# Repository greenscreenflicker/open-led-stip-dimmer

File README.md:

# open-led-stip-dimmer
This is an open led stipe dimmer for MakerCon 2017 (16.2-18.2) in Heidelberg, Germany.
The project is used as sample project to explain the basics of PCB layout.

# Tutorial
The script (in German) can be found in the folder "doc".

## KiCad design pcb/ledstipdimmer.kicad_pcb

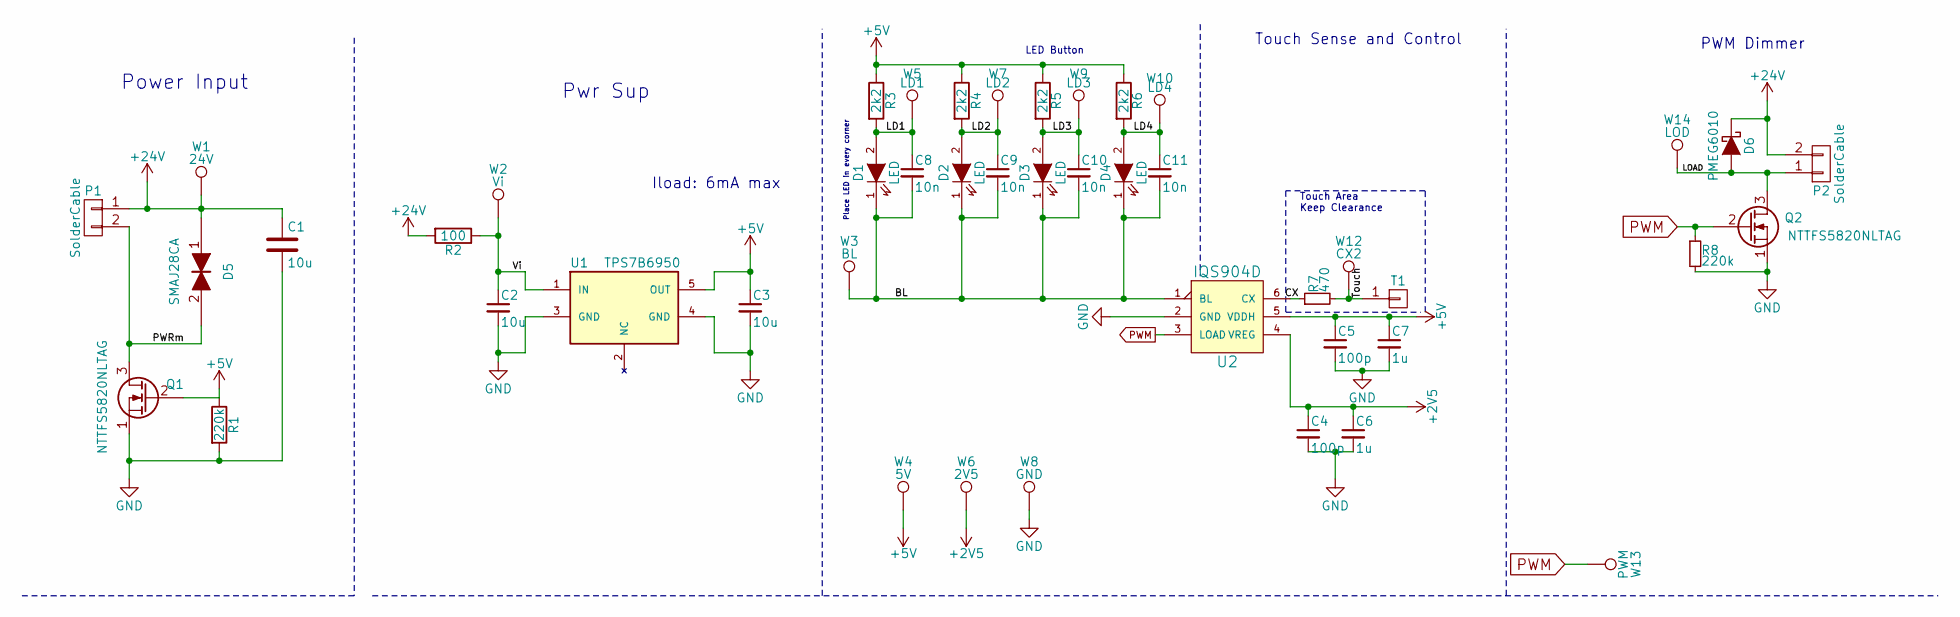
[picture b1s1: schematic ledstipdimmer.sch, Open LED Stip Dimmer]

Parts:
C1, C2: 10u; SMD-C-1206; Voltage 50V
C3: 10u; SMD-C-0603; Voltage 10V
C4, C5: 100p; SMD-C-0603; Voltage 10V
C6, C7: 1u; SMD-C-0603; Voltage 10V
C8, C9, C10, C11: 10n; SMD-C-0603; Voltage 50V
D1, D2, D3, D4: LED; LED_1206_revmnt
D5: SMAJ28CA; SMA_Bipolar
D6: PMEG6010; SOD-123
P1, P2: SolderCable; solder_cable_2
Q1, Q2: NTTFS5820NLTAG; WDFN8_3.3x3.3
R1, R8: 220k; SMD-R-0603
R2: 100; SMD-R-0603
R3, R4, R5, R6: 2k2; SMD-R-0603
R7: 470; SMD-R-0603
T1: TOUCH; touch15x15
U1: TPS7B6950; SOT-23-5; Mouser# 595-TPS7B6950DBVR
U2: IQS904D; SOT-23-6; Mouser# IQS904D-00000TSR
W1: 24V; RECP_709150001050006
W2: Vi; RECP_709150001050006
W3: BL; RECP_709150001050006
W4: 5V; RECP_709150001050006
W5: LD1; RECP_709150001050006
W6: 2V5; RECP_709150001050006
W7: LD2; RECP_709150001050006
W8: GND; RECP_709150001050006
W9: LD3; RECP_709150001050006
W10: LD4; RECP_709150001050006
W12: CX2; RECP_709150001050006
W13: PWM; RECP_709150001050006
W14: LOD; RECP_709150001050006

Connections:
+2V5: C4.1, C6.1, U2.4 (VREG), W6.1
+5V: C3.1, C5.1, C7.1, Q1.2 (G), R1.1, R3.1, R4.1, R5.1, R6.1, U1.5 (OUT), U2.5 (VDDH), W4.1
+24V: C1.1, D5.1, D6.1 (K), P1.1, P2.2, R2.2, W1.1
/BL: C8.2, C9.2, C10.2, C11.2, D1.1 (K), D2.1 (K), D3.1 (K), D4.1 (K), U2.1 (BL), W3.1
/CX: R7.1, U2.6 (CX)
/LD1: C8.1, D1.2 (A), R3.2, W5.1
/LD2: C9.1, D2.2 (A), R4.2, W7.1
/LD3: C10.1, D3.2 (A), R5.2, W9.1
/LD4: C11.1, D4.2 (A), R6.2, W10.1
/LOAD: D6.2 (A), P2.1, Q2.3 (D), W14.1
/PWRm: D5.2, P1.2, Q1.3 (D)
/Touch: R7.2, T1.1, W12.1
/Vi: C2.1, R2.1, U1.1 (IN), W2.1
GND: C1.2, C2.2, C3.2, C4.2, C5.2, C6.2, C7.2, Q1.1 (S), Q2.1 (S), R1.2, R8.2, U1.3 (GND), U1.4 (GND), U2.2 (GND), W8.1
PWM: Q2.2 (G), R8.1, U2.3 (LOAD), W13.1

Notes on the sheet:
Touch Sense and Control
Power Input
Pwr Sup
Iload: 6mA max
LED Button
PWM Dimmer
Place LED in every corner
Touch Area Keep Clearance

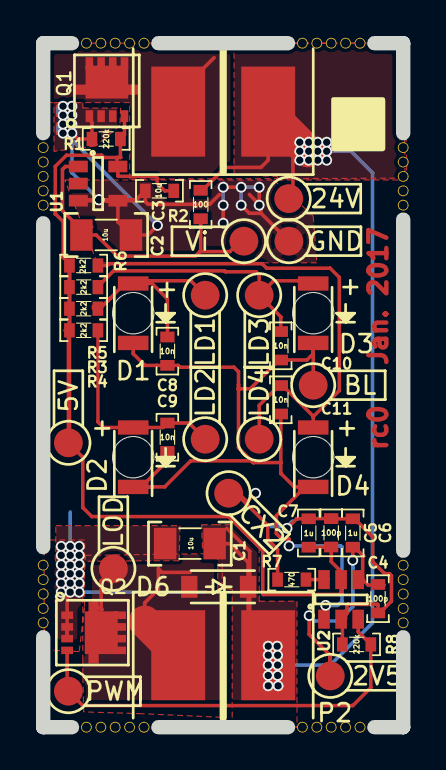
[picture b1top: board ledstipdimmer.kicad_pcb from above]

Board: 2 copper layers, 20.0 x 38.0 mm, 43 parts (0 on the bottom side), 15 nets.

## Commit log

2016-12-30 Inital schematic design.
2016-12-31 PCB design waiting for review.
2017-01-01 Resolved DRC conflicts. Adjustments left.
2017-01-04 Produced panel and corresponding gerber files.
2017-01-05 Updated files.
2017-01-11 Production adjustments for Aetzwerk (Solder Resist with reduces for enhanced quality).
2017-02-08 Uploaded script.
